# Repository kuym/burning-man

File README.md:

Burning Man 2015

aka Church of the Fifth Element
aka Home Sweet Dome
aka Burners on the Fence

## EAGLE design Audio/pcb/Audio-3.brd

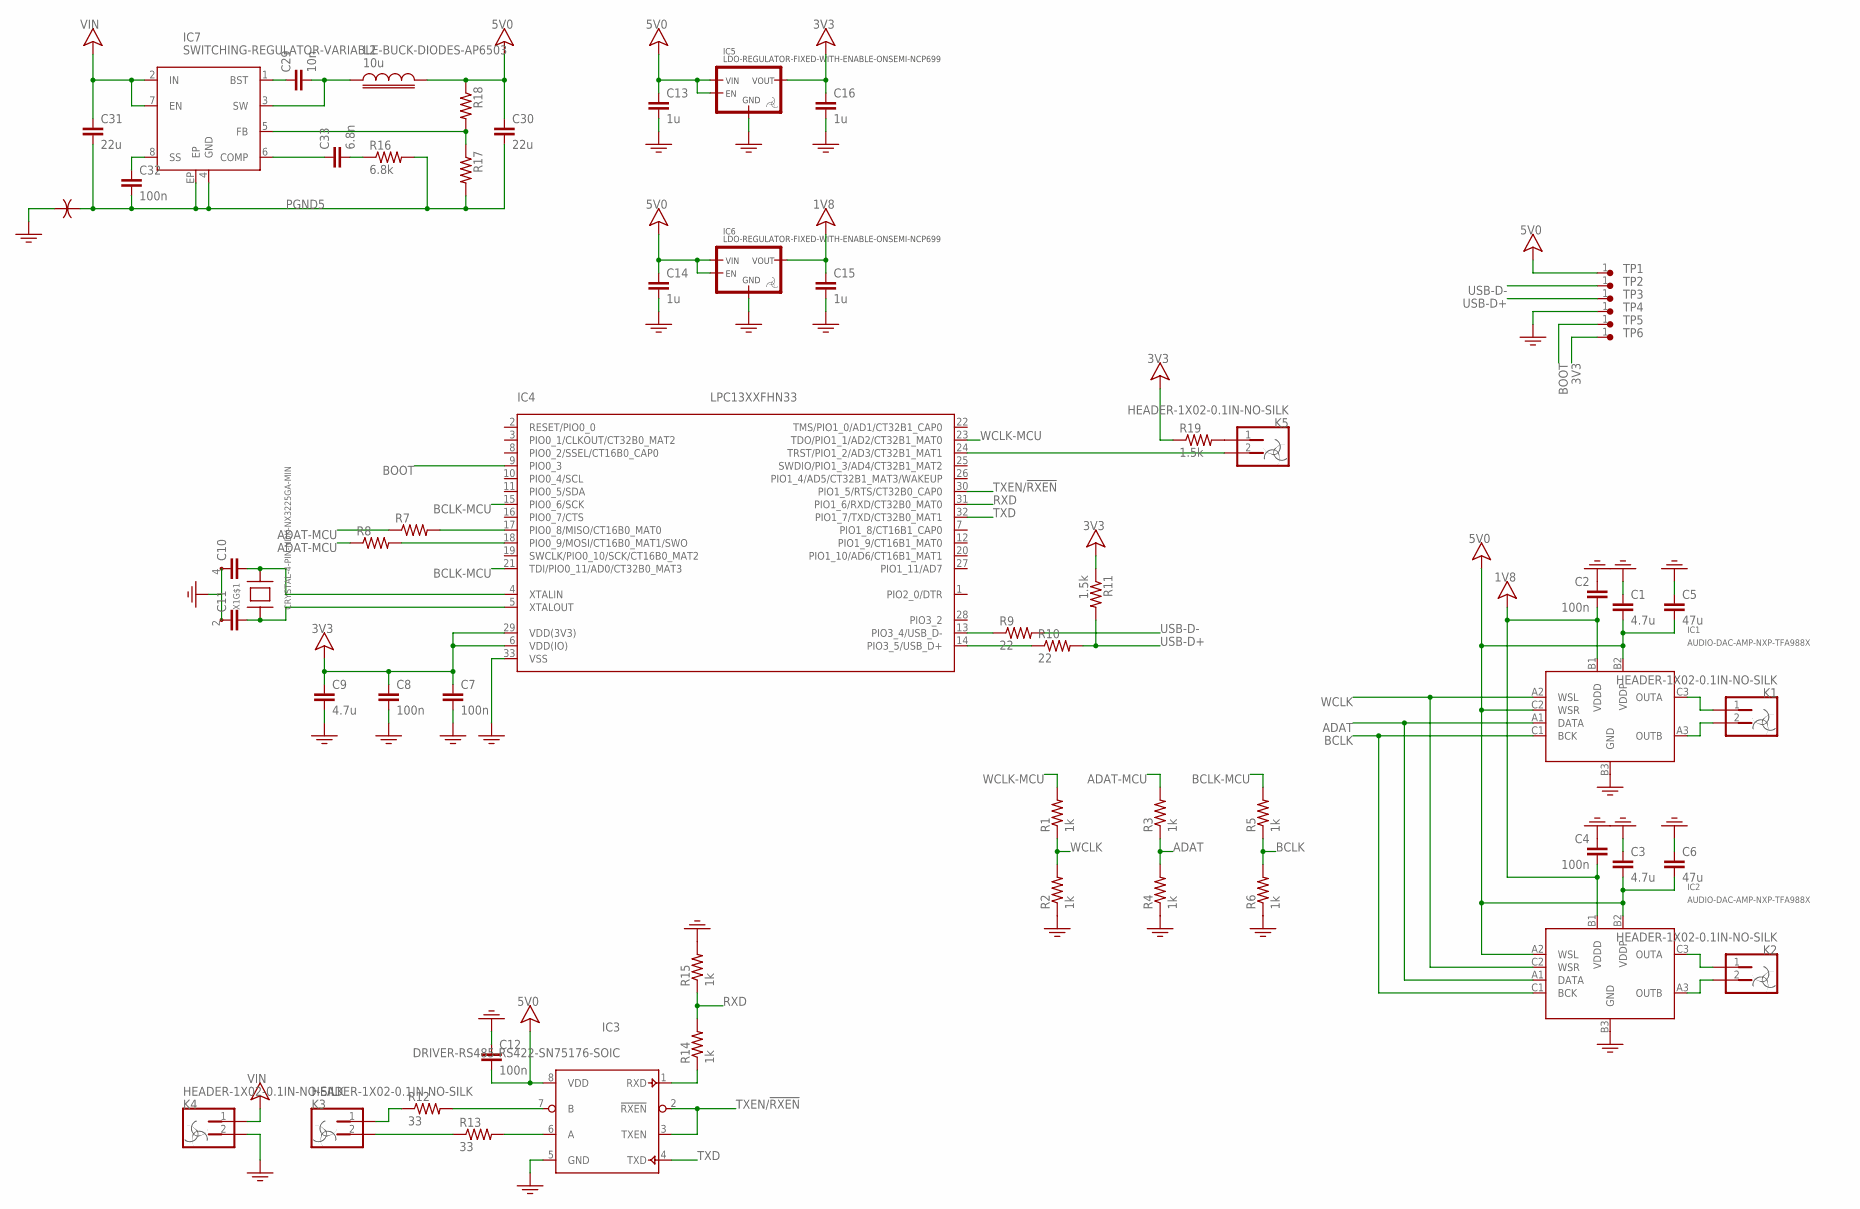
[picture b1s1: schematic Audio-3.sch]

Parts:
C1, C3, C9: 4.7u; 0603-MIN
C2, C4, C7, C8, C12, C32: 100n; 0603-MIN
C5, C6: 47u; 1206-MIN
C10, C11: CAP-0603-MIN; 0603-MIN
C13, C14, C15, C16: 1u; 0603-MIN
C29: 10n; 0603-MIN
C30, C31: 22u; 1206
C33: 6.8n; 0603-MIN
IC1, IC2: AUDIO-DAC-AMP-NXP-TFA988X; NXP-TFA988X-WLCSP9
IC3: DRIVER-RS485-RS422-SN75176-SOIC; EIAJ-SOIC8
IC4: LPC13XXFHN33; HVQFN33-7X7MM
IC5, IC6: LDO-REGULATOR-FIXED-WITH-ENABLE-ONSEMI-NCP699; SOT23-5
IC7: SWITCHING-REGULATOR-VARIABLE-BUCK-DIODES-AP6503; EIAJ-SOIC8-3.9MM-EXPOSED-PAD
K1, K2, K3, K4, K5: HEADER-1X02-0.1IN-NO-SILK; HEADER-1X02-NO-SILK
L2: 10u; 1210
R1, R2, R3, R4, R5, R6, R14, R15: 1k; 0603-MIN
R7, R8, R17, R18: RESISTOR-0603-MIN; 0603-MIN
R9, R10: 22; 0603-MIN
R11, R19: 1.5k; 0603-MIN
R12, R13: 33; 0805-MIN
R16: 6.8k; 0603-MIN
TP1, TP2, TP3, TP4, TP5, TP6: TEST-POINT-0.75MM
U4: GND-ISOLATOR-0.032"
X1: CRYSTAL-4-PIN-NDK-NX3225GA-MIN; CRYSTAL-NDK-NX3225GA-3X2.5MM-MIN

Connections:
1V8: C2.1, C4.1, C15.2, IC1.B1 (VDDD), IC2.B1 (VDDD), IC6.5 (VOUT)
3V3: C7.2, C8.2, C9.2, C16.2, IC4.6 (VDD(IO)), IC4.29 (VDD(3V3)), IC5.5 (VOUT), R11.1, R19.1, TP6.1
5V0: C1.1, C3.1, C5.1, C6.1, C12.1, C13.2, C14.2, C30.2, IC1.B2 (VDDP), IC1.C2 (WSR), IC2.A2 (WSL), IC2.B2 (VDDP), IC3.8 (VDD), IC5.1 (VIN), IC5.3 (EN), IC6.1 (VIN), IC6.3 (EN), L2.2, R18.1, TP1.1
5V0FB: IC7.5 (FB), R17.1, R18.2
ADAT: IC1.A1 (DATA), IC2.A1 (DATA), R3.1, R4.2
ADAT-MCU: R3.2, R7.1, R8.1
BCLK: IC1.C1 (BCK), IC2.C1 (BCK), R5.1, R6.2
BCLK-MCU: IC4.15 (PIO0_6/SCK), IC4.21 (TDI/PIO0_11/AD0/CT32B0_MAT3), R5.2
BOOT: IC4.9 (PIO0_3), TP5.1
GND: C1.2, C2.2, C3.2, C4.2, C5.2, C6.2, C7.1, C8.1, C9.1, C10.2, C11.2, C12.2, C13.1, C14.1, C15.1, C16.1, IC1.B3 (GND), IC2.B3 (GND), IC3.5 (GND), IC4.33 (VSS), IC5.2 (GND), IC6.2 (GND), K4.2, R2.1, R4.1, R6.1, R15.2, TP4.1, U4.B, X1.2 (1), X1.4 (1)
unnamed: IC4.17 (PIO0_8/MISO/CT16B0_MAT0), R7.2
unnamed: IC4.18 (PIO0_9/MOSI/CT16B0_MAT1/SWO), R8.2
unnamed: C10.1, IC4.4 (XTALIN), X1.3
unnamed: C11.1, IC4.5 (XTALOUT), X1.1
unnamed: IC4.13 (PIO3_4/USB_D-), R9.1
unnamed: IC4.14 (PIO3_5/USB_D+), R10.1
unnamed: IC3.7 (B), R12.2
unnamed: IC1.C3 (OUTA), K1.1
unnamed: IC1.A3 (OUTB), K1.2
unnamed: IC2.C3 (OUTA), K2.1
unnamed: IC2.A3 (OUTB), K2.2
unnamed: IC3.6 (A), R13.2
unnamed: C29.1, IC7.3 (SW), L2.1
unnamed: IC3.1 (RXD), R14.1
unnamed: C29.2, IC7.1 (BST)
unnamed: C33.2, IC7.6 (COMP)
unnamed: C33.1, R16.1
unnamed: K3.2, R13.1
unnamed: K3.1, R12.1
unnamed: C32.2, IC7.8 (SS)
unnamed: K5.1, R19.2
unnamed: IC4.24 (TRST/PIO1_2/AD3/CT32B1_MAT1), K5.2
PGND5: C30.1, C31.1, C32.1, IC7.4 (GND), IC7.EP, R16.2, R17.2, U4.A
RXD: IC4.31 (PIO1_6/RXD/CT32B0_MAT0), R14.2, R15.1
TXD: IC3.4 (TXD), IC4.32 (PIO1_7/TXD/CT32B0_MAT1)
TXEN/!RXEN: IC3.2 (!RXEN), IC3.3 (TXEN), IC4.30 (PIO1_5/RTS/CT32B0_CAP0)
USB-D+: R10.2, R11.2, TP3.1
USB-D-: R9.2, TP2.1
VIN: C31.2, IC7.2 (IN), IC7.7 (EN), K4.1
WCLK: IC1.A2 (WSL), IC2.C2 (WSR), R1.1, R2.2
WCLK-MCU: IC4.23 (TDO/PIO1_1/AD2/CT32B1_MAT0), R1.2

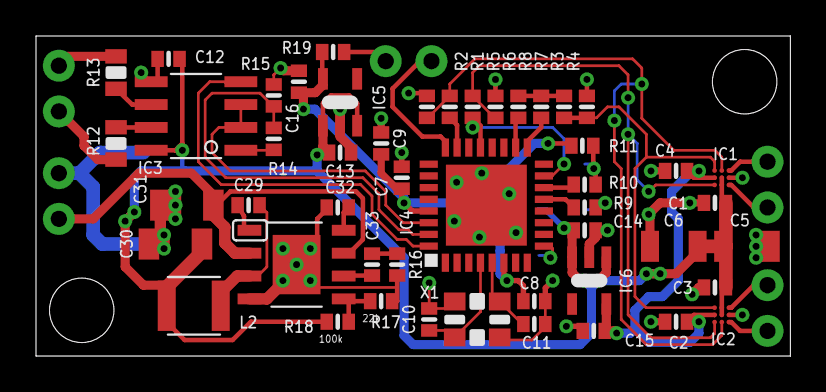
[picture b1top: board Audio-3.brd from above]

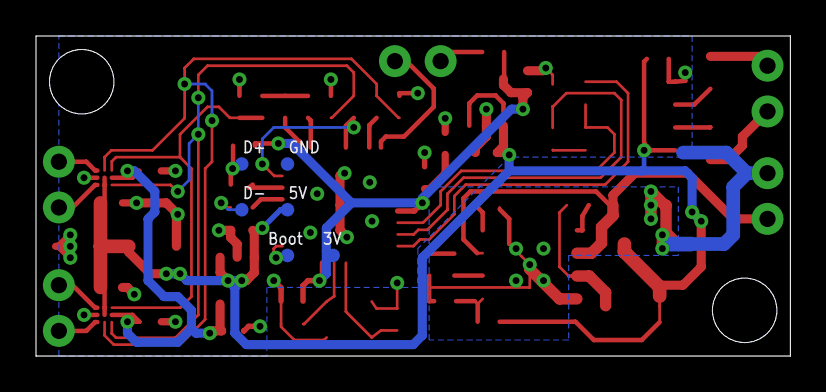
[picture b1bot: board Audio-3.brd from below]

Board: 2 copper layers, 41.9 x 17.8 mm, 61 parts (7 on the bottom side), 41 nets.

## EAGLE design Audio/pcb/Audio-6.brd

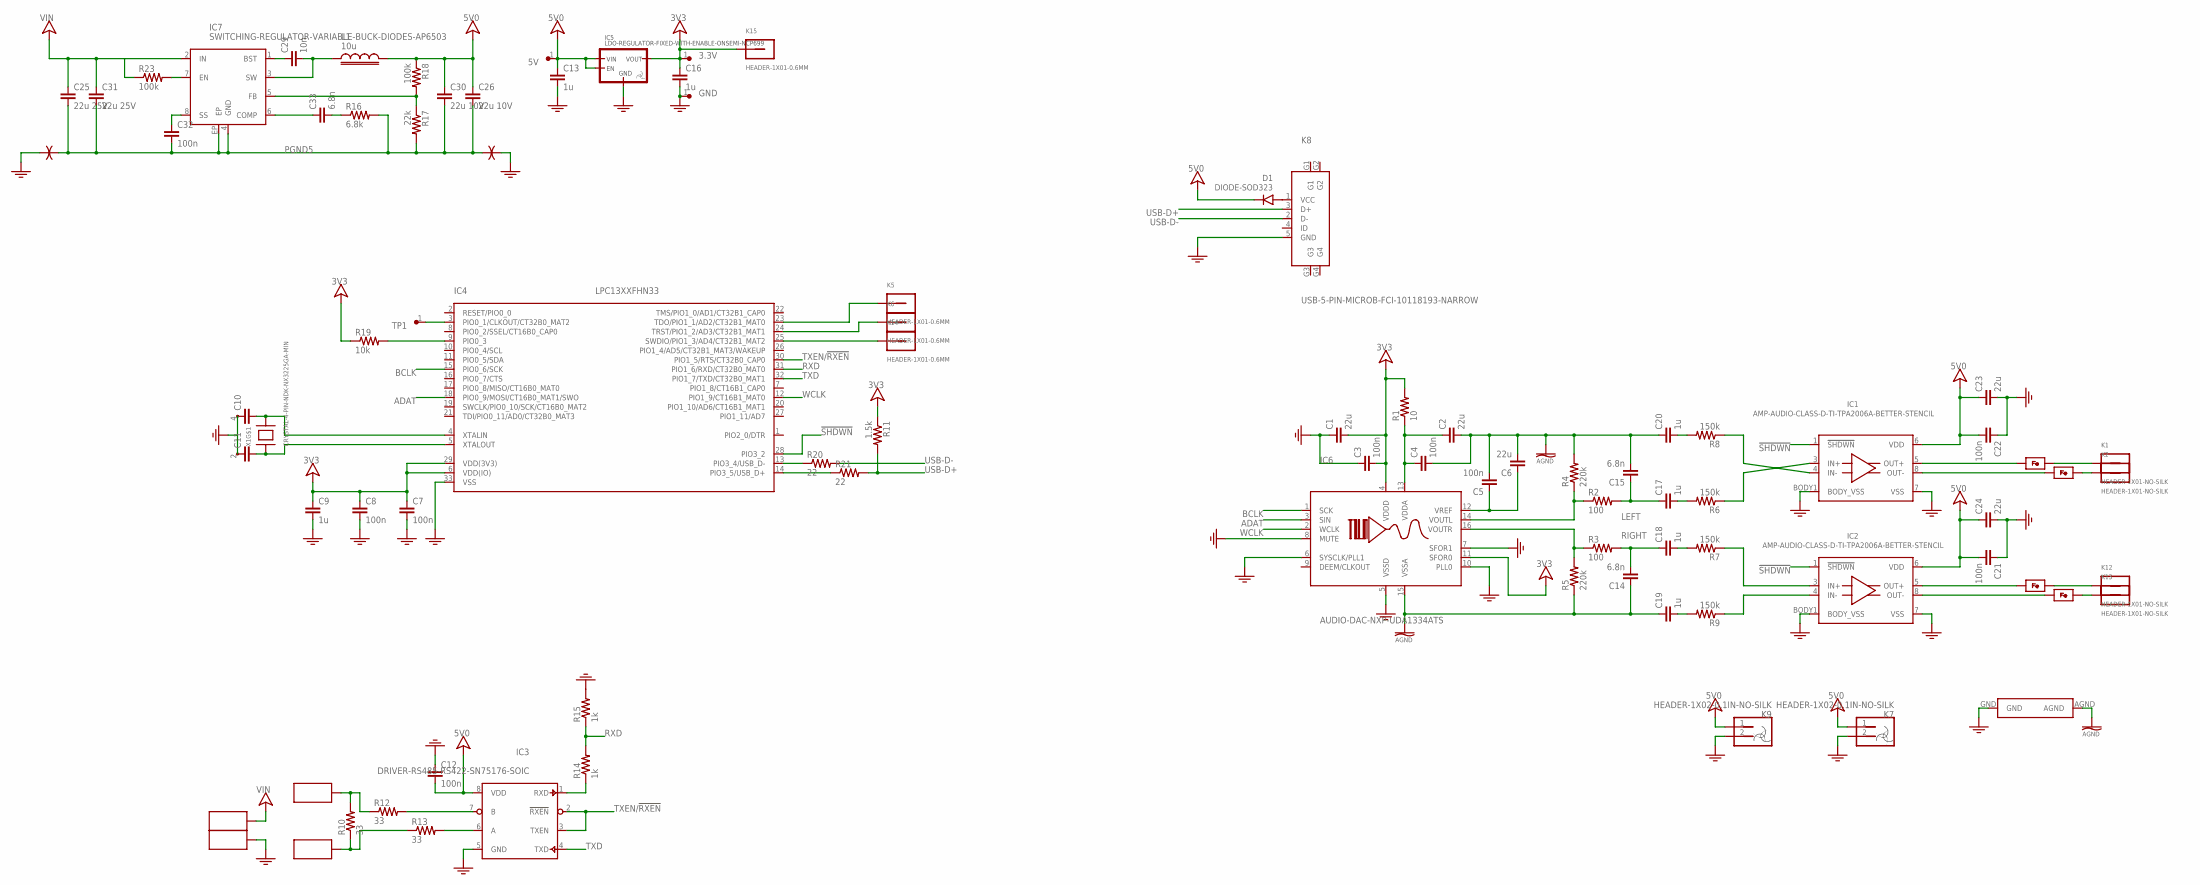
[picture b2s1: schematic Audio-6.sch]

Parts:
3.3V, 5V: TEST-POINT-0.75MM
C1, C2, C6, C23, C24: 22u; 1206-MIN
C3, C4, C5, C7, C8, C12, C21, C22, C32: 100n; 0603-MIN
C9, C13, C16, C17, C18, C19, C20: 1u; 0603-MIN
C10, C11: CAP-0603-MIN; 0603-MIN
C14, C15, C33: 6.8n; 0603-MIN
C25, C31: 22u 25V; 1206
C26, C30: 22u 10V; 1206
C29: 10n; 0603-MIN
D1: DIODE-SOD323; SOD323
FB1, FB2, FB3, FB4: FERRITE-BEAD-0603-MIN; 0603-MIN
GND: TEST-POINT-0.75MM
IC1, IC2: AMP-AUDIO-CLASS-D-TI-TPA2006A-BETTER-STENCIL; QFN8-3X3MM-TI-TPA200X-BETTER-STENCIL
IC3: DRIVER-RS485-RS422-SN75176-SOIC; EIAJ-SOIC8
IC4: LPC13XXFHN33; HVQFN33-7X7MM
IC5: LDO-REGULATOR-FIXED-WITH-ENABLE-ONSEMI-NCP699; SOT23-5
IC6: AUDIO-DAC-NXP-UDA1334ATS; TSSOP16
IC7: SWITCHING-REGULATOR-VARIABLE-BUCK-DIODES-AP6503; EIAJ-SOIC8-3.9MM-EXPOSED-PAD
K1, K2, K12, K13: HEADER-1X01-NO-SILK
K3, K4, K10, K11: SPEAKER-BLOCK
K5, K6, K14, K15: HEADER-1X01-0.6MM; HEADER-1X01-0.6MM-DIAM
K7, K9: HEADER-1X02-0.1IN-NO-SILK; HEADER-1X02-NO-SILK
K8: USB-5-PIN-MICROB-FCI-10118193-NARROW; USB-MICROB-FCI-10118193-NARROW
L1: 10u; INDUCTOR-SMD-6X6MM
R1: 10; 0603-MIN
R2, R3: 100; 0603-MIN
R4, R5: 220k; 0603-MIN
R6, R7, R8, R9: 150k; 0603-MIN
R10, R12, R13: 33; 0805-MIN
R11: 1.5k; 0603-MIN
R14, R15: 1k; 0603-MIN
R16: 6.8k; 0603-MIN
R17: 22k; 0603-MIN
R18, R23: 100k; 0603-MIN
R19: 10k; 0603-MIN
R20, R21: 22; 0603-MIN
TP1: TEST-POINT-0.75MM
U1, U4: GND-ISOLATOR-0.032"
U$4: GND-AGND-CONNECTION
X1: CRYSTAL-4-PIN-NDK-NX3225GA-MIN; CRYSTAL-NDK-NX3225GA-3X2.5MM-MIN

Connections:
3V3: 3.3V.1, C1.1, C3.1, C7.2, C8.2, C9.2, C16.2, IC4.6 (VDD(IO)), IC4.29 (VDD(3V3)), IC5.5 (VOUT), IC6.4 (VDDD), IC6.11 (SFOR0), K15.P$1, R1.2, R11.1, R19.1
5V0: 5V.1, C12.1, C13.2, C21.1, C22.1, C23.2, C24.2, C26.2, C30.2, D1.K, IC1.6 (VDD), IC2.6 (VDD), IC3.8 (VDD), IC5.1 (VIN), IC5.3 (EN), K7.1, K9.1, L1.2, R18.1
5V0FB: IC7.5 (FB), R17.1, R18.2
!SHDWN: IC1.1 (!SHDWN), IC2.1 (!SHDWN), IC4.28 (PIO3_2)
ADAT: IC4.18 (PIO0_9/MOSI/CT16B0_MAT1/SWO), IC6.3 (SIN)
AGND: C2.1, C4.1, C5.1, C6.1, C14.2, C15.1, C19.2, C20.2, IC6.15 (VSSA), R4.2, R5.1, U$4.AGND
BCLK: IC4.15 (PIO0_6/SCK), IC6.1 (SCK)
BOOT: IC4.3 (PIO0_1/CLKOUT/CT32B0_MAT2), TP1.1
D+: IC4.14 (PIO3_5/USB_D+), R21.1
D-: IC4.13 (PIO3_4/USB_D-), R20.1
GND: C1.2, C3.2, C7.1, C8.1, C9.1, C10.2, C11.2, C12.2, C13.1, C16.1, C21.2, C22.2, C23.1, C24.1, GND.1, IC1.7 (VSS), IC1.BODY1 (BODY_VSS), IC2.7 (VSS), IC2.BODY1 (BODY_VSS), IC3.5 (GND), IC4.33 (VSS), IC5.2 (GND), IC6.5 (VSSD), IC6.6 (SYSCLK/PLL1), IC6.7 (SFOR1), IC6.8 (MUTE), IC6.10 (PLL0), K4.P$1, K7.2, K8.5 (GND), K9.2, R15.2, U1.A, U4.B, U$4.GND, X1.2 (1), X1.4 (1)
IC1-: IC1.4 (IN-), R8.1
IC1OUT+: FB1.2, K1.1
IC1OUT-: FB2.2, K2.1
IC1SE: IC6.14 (VOUTL), R2.1, R4.1
IC2+: IC2.3 (IN+), R7.1
IC2-: IC2.4 (IN-), R9.1
IC2OUT+: FB3.2, K12.1
IC2OUT-: FB4.2, K13.1
IC2SE: IC6.16 (VOUTR), R3.1, R5.2
IO1: IC4.23 (TDO/PIO1_1/AD2/CT32B1_MAT0), K5.P$1
IO2: IC4.24 (TRST/PIO1_2/AD3/CT32B1_MAT1), K6.P$1
IO3: IC4.25 (SWDIO/PIO1_3/AD4/CT32B1_MAT2), K14.P$1
LEFT: C15.2, C17.2, R2.2
unnamed: IC1.3 (IN+), R6.1
unnamed: IC4.9 (PIO0_3), R19.2
unnamed: C10.1, IC4.4 (XTALIN), X1.3
unnamed: C11.1, IC4.5 (XTALOUT), X1.1
unnamed: IC3.7 (B), R12.2
unnamed: C17.1, R6.2
unnamed: C18.1, R7.2
unnamed: IC3.6 (A), R13.2
unnamed: C29.1, IC7.3 (SW), L1.1
unnamed: IC3.1 (RXD), R14.1
unnamed: C29.2, IC7.1 (BST)
unnamed: C33.2, IC7.6 (COMP)
unnamed: C33.1, R16.1
unnamed: C32.2, IC7.8 (SS)
unnamed: D1.A, K8.1 (VCC)
unnamed: C2.2, C4.2, IC6.13 (VDDA), R1.1
unnamed: IC7.7 (EN), R23.2
unnamed: C19.1, R9.2
unnamed: C20.1, R8.2
unnamed: FB1.1, IC1.5 (OUT+)
unnamed: FB2.1, IC1.8 (OUT-)
unnamed: FB3.1, IC2.5 (OUT+)
unnamed: FB4.1, IC2.8 (OUT-)
PGND5: C25.1, C26.1, C30.1, C31.1, C32.1, IC7.4 (GND), IC7.EP, R16.2, R17.2, U1.B, U4.A
RIGHT: C14.1, C18.2, R3.2
RS485D+: K11.P$1, R10.1, R13.1
RS485D-: K10.P$1, R10.2, R12.1
RXD: IC4.31 (PIO1_6/RXD/CT32B0_MAT0), R14.2, R15.1
TXD: IC3.4 (TXD), IC4.32 (PIO1_7/TXD/CT32B0_MAT1)
TXEN/!RXEN: IC3.2 (!RXEN), IC3.3 (TXEN), IC4.30 (PIO1_5/RTS/CT32B0_CAP0)
USB-D+: K8.3 (D+), R11.2, R21.2
USB-D-: K8.2 (D-), R20.2
VIN: C25.2, C31.2, IC7.2 (IN), K3.P$1, R23.1
VREF: C5.2, C6.2, IC6.12 (VREF)
WCLK: IC4.12 (PIO1_9/CT16B1_MAT0), IC6.2 (WCLK)

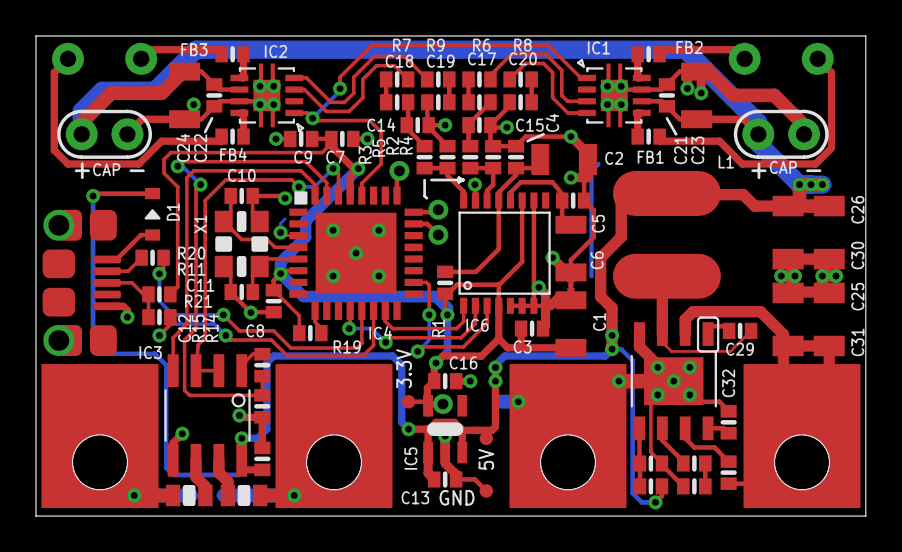
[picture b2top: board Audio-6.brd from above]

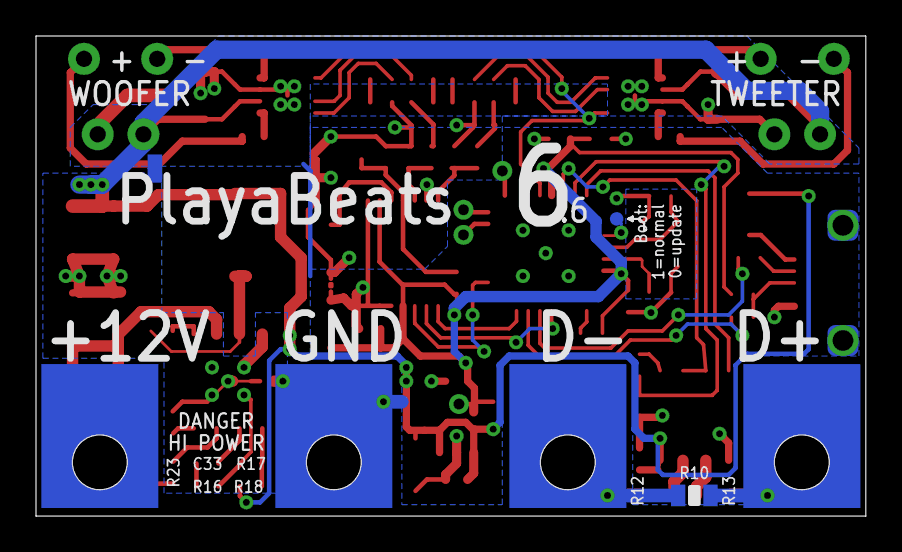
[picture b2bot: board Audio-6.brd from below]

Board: 2 copper layers, 46.1 x 26.7 mm, 89 parts (7 on the bottom side), 59 nets.

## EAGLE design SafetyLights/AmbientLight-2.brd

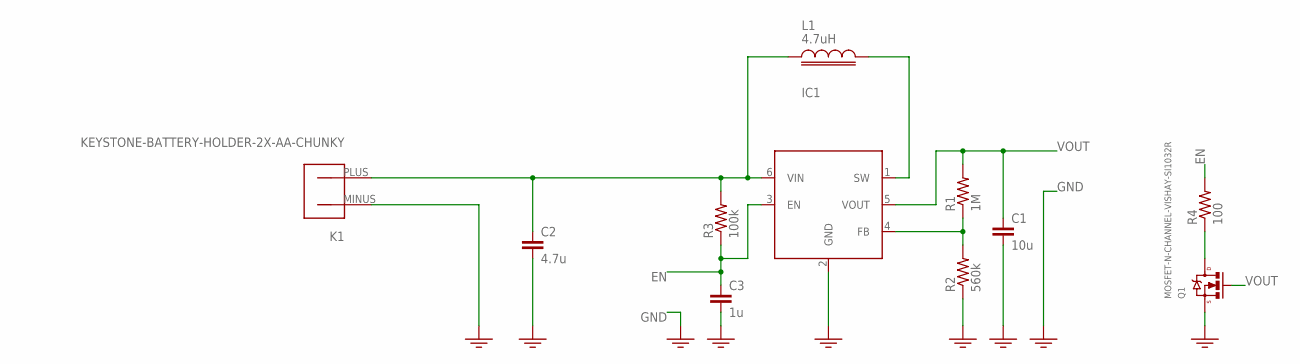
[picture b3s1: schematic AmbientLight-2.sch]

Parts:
C1: 10u; 0805-WIDE
C2: 4.7u; 0603-MIN
C3: 1u; 0603-MIN
IC1: SWITCHING-REGULATOR-VARIABLE-BOOST-MCP1640; SOT23-6
K1: KEYSTONE-BATTERY-HOLDER-2X-AA-CHUNKY
L1: 4.7uH; 1210-INDUCTOR-MIN
Q1: MOSFET-N-CHANNEL-VISHAY-SI1032R; SC-75A
R1: 1M; 0603-MIN
R2: 560k; 0603-MIN
R3: 100k; 0603-MIN
R4: 100; 0603-MIN

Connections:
EN: C3.2, IC1.3 (EN), R3.1, R4.2
GND: C1.1, C2.1, C3.1, IC1.2 (GND), K1.MINUS (PLUS), Q1.2 (SOURCE), R2.1
unnamed: Q1.3 (DRAIN), R4.1
VBAT: C2.2, IC1.6 (VIN), K1.PLUS (MINUS), L1.1, R3.2
VFB: IC1.4 (FB), R1.1, R2.2
VOUT: C1.2, IC1.5 (VOUT), Q1.1 (GATE), R1.2
VSW: IC1.1 (SW), L1.2

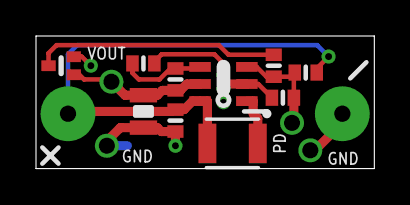
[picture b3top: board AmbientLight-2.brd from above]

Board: 2 copper layers, 18.8 x 7.4 mm, 11 parts (0 on the bottom side), 7 nets.

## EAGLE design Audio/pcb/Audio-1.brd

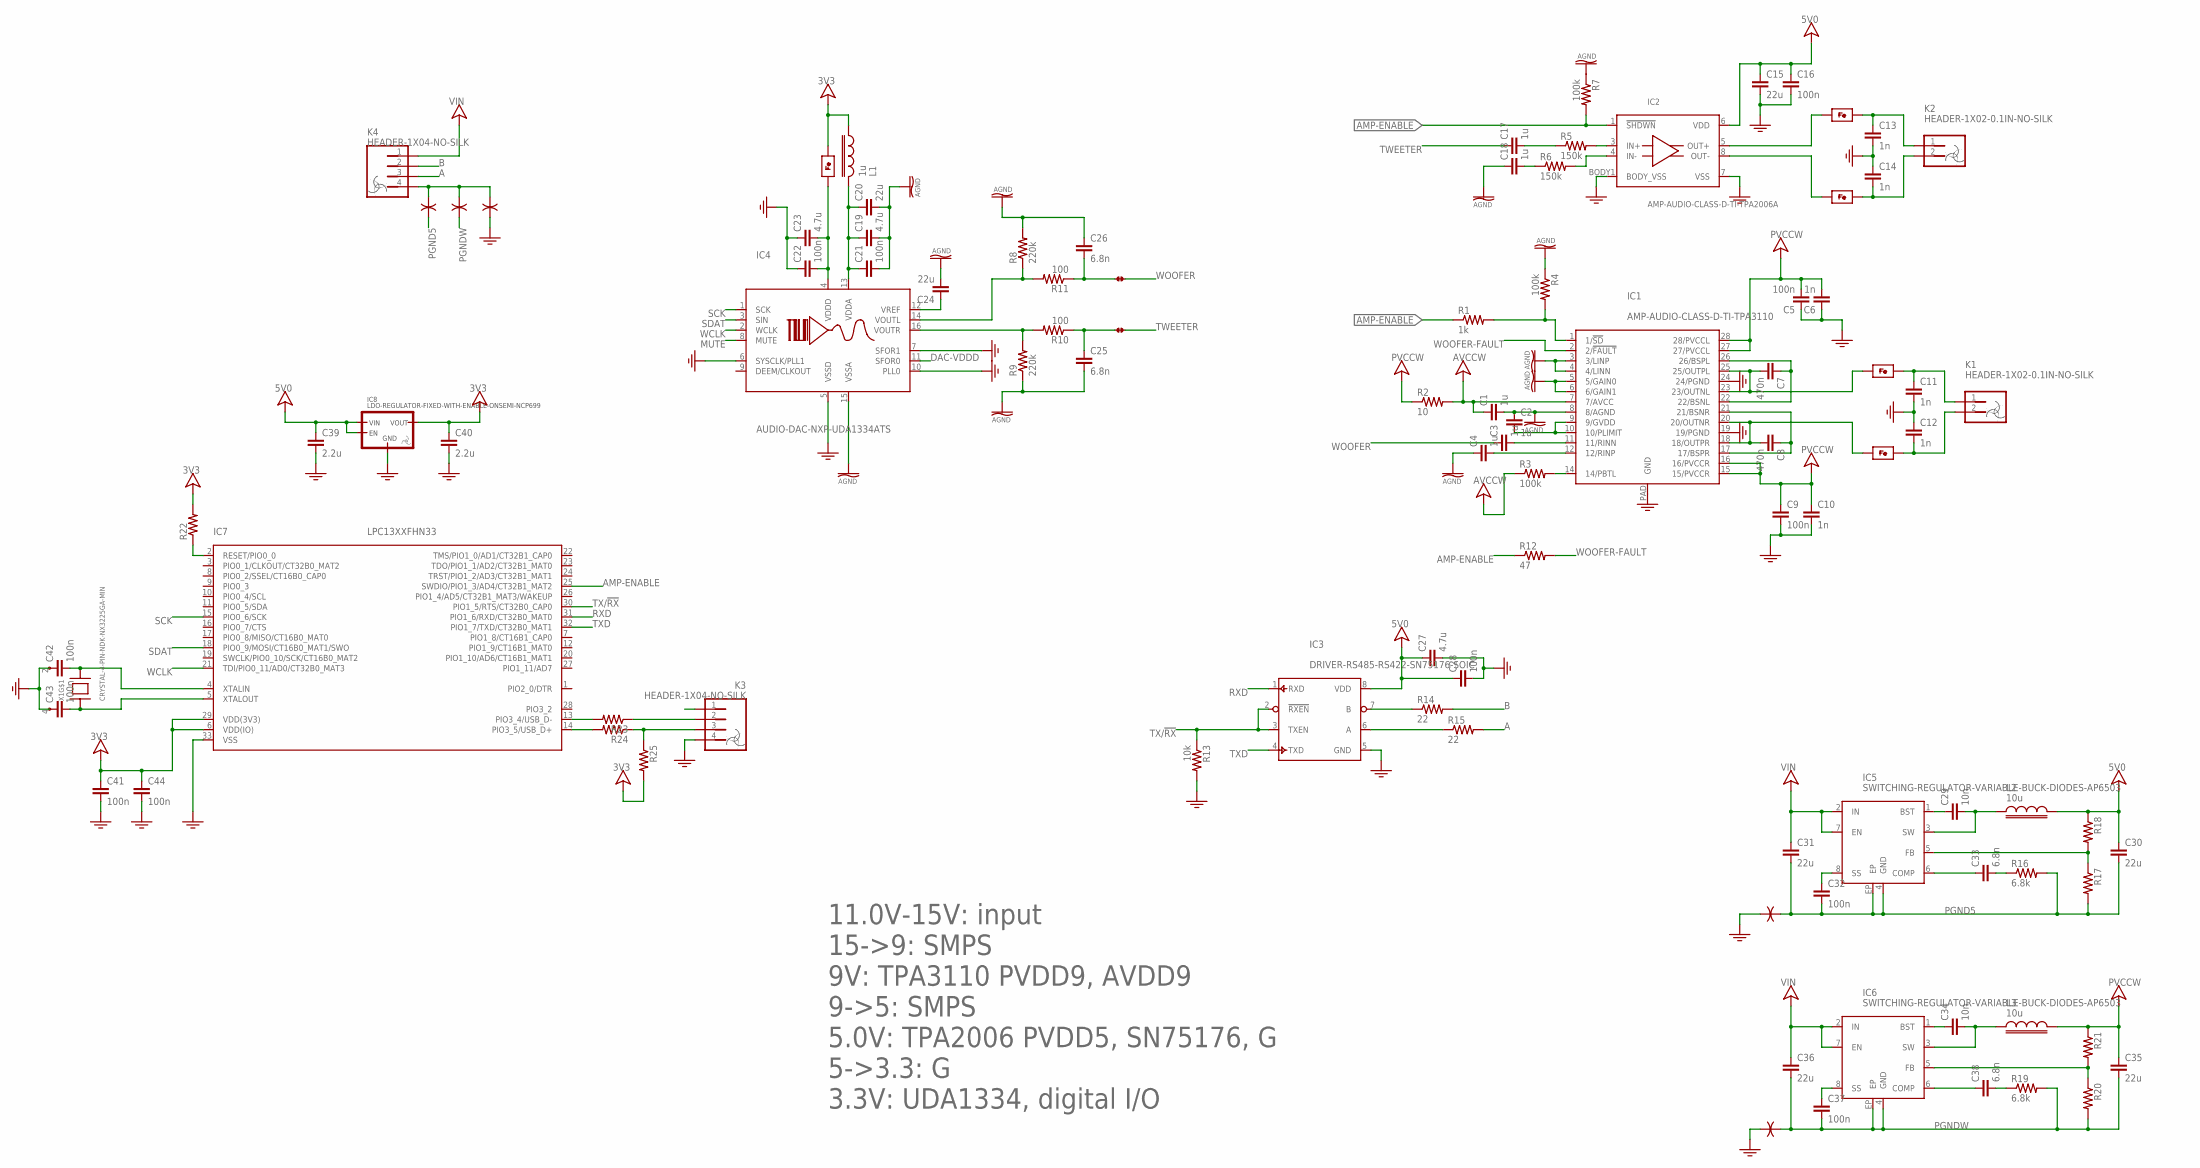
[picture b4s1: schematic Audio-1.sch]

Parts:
C1, C2, C3, C4, C17, C18: 1u; 0603-MIN
C5, C9, C16, C21, C22, C28, C32, C37, C41, C42, C43, C44: 100n; 0603-MIN
C6, C10, C11, C12, C13, C14: 1n; 0603-MIN
C7, C8: 470n; 0603-MIN
C15, C20, C24: 22u; 1206-MIN
C19, C23: 4.7u; 0805-WIDE
C25, C26: 6.8n; 0603
C27: 4.7u; 0805
C29, C34: 10n; 0603-MIN
C30, C31, C35, C36: 22u; 1206
C33, C38: 6.8n; 0603-MIN
C39, C40: 2.2u; 0603-MIN
FB1, FB2, FB3, FB4, FB5: FERRITE-BEAD-0603-MIN; 0603-MIN
IC1: AMP-AUDIO-CLASS-D-TI-TPA3110; SSOP28-5.3MM-POWERPAD
IC2: AMP-AUDIO-CLASS-D-TI-TPA2006A; QFN8-3X3MM-TI-TPA200X
IC3: DRIVER-RS485-RS422-SN75176-SOIC; EIAJ-SOIC8
IC4: AUDIO-DAC-NXP-UDA1334ATS; TSSOP16
IC5, IC6: SWITCHING-REGULATOR-VARIABLE-BUCK-DIODES-AP6503; EIAJ-SOIC8-3.9MM-EXPOSED-PAD
IC7: LPC13XXFHN33; HVQFN33-7X7MM
IC8: LDO-REGULATOR-FIXED-WITH-ENABLE-ONSEMI-NCP699; SOT23-5
J1, J2: JUMPER-0805; 0805-JUMPER
K1, K2: HEADER-1X02-0.1IN-NO-SILK; HEADER-1X02-NO-SILK
K3, K4: HEADER-1X04-NO-SILK
L1: 1u; 0805-MIN
L2, L3: 10u; 1210
R1: 1k; 0603-MIN
R2: 10; 0603-MIN
R3, R4, R7: 100k; 0603-MIN
R5, R6: 150k; 0603-MIN
R8, R9: 220k; 0603
R10, R11: 100; 0603
R12: 47; 0603-MIN
R13: 10k; 0603-MIN
R14, R15: 22; 0805-MIN
R16, R19: 6.8k; 0603-MIN
R17, R18, R20, R21, R22, R23, R24, R25: RESISTOR-0603-MIN; 0603-MIN
U1, U2, U3, U4, U5: GND-ISOLATOR-0.032"
X1: CRYSTAL-4-PIN-NDK-NX3225GA-MIN; CRYSTAL-NDK-NX3225GA-3X2.5MM-MIN

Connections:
3V3: C40.2, C41.2, C44.2, FB5.2, IC7.6 (VDD(IO)), IC7.29 (VDD(3V3)), IC8.5 (VOUT), L1.2, R22.2, R25.2
5V0: C15.2, C16.2, C27.2, C28.2, C30.2, C39.2, IC2.6 (VDD), IC3.8 (VDD), IC8.1 (VIN), IC8.3 (EN), L2.2, R18.1
5V0FB: IC5.5 (FB), R17.1, R18.2
!WOOFER-SD: IC1.1 (1/!SD), R1.2, R4.2
A: K4.3, R15.2
AGND: C1.1, C2.2, C4.2, C18.2, C19.1, C20.1, C21.1, C24.1, C25.1, C26.2, IC1.3 (3/LINP), IC1.4 (4/LINN), IC1.5 (5/GAIN0), IC1.6 (6/GAIN1), IC1.8 (8/AGND), IC4.15 (VSSA), R4.1, R7.1, R8.2, R9.1
AMP-ENABLE: IC2.1 (!SHDWN), IC7.25 (SWDIO/PIO1_3/AD4/CT32B1_MAT2), R1.1, R7.2, R12.1
AVCCW: C1.2, IC1.7 (7/AVCC), R2.2, R3.1
B: K4.2, R14.2
BSL: C7.2, IC1.22 (22/BSNL), IC1.26 (26/BSPL)
BSR: C8.2, IC1.17 (17/BSPR), IC1.21 (21/BSNR)
D+: K3.3, R24.1, R25.1
D-: K3.2, R23.1
DAC-TO: C25.2, J2.1, R10.1
DAC-VDDA: C19.2, C20.2, C21.2, IC4.13 (VDDA), L1.1
DAC-VDDD: C22.1, C23.1, FB5.1, IC4.4 (VDDD), IC4.11 (SFOR0)
DAC-VOUT-TO: IC4.16 (VOUTR), R9.2, R10.2
DAC-VOUT-WO: IC4.14 (VOUTL), R8.1, R11.2
DAC-WO: C26.1, J1.1, R11.1
GND: C5.2, C6.2, C9.1, C10.1, C11.1, C12.2, C13.1, C14.2, C15.1, C16.1, C22.2, C23.2, C27.1, C28.1, C39.1, C40.1, C41.1, C42.2, C43.2, C44.1, IC1.19 (19/PGND), IC1.24 (24/PGND), IC1.PAD (GND), IC2.7 (VSS), IC2.BODY1 (BODY_VSS), IC3.5 (GND), IC4.5 (VSSD), IC4.6 (SYSCLK/PLL1), IC4.7 (SFOR1), IC4.10 (PLL0), IC7.33 (VSS), IC8.2 (GND), K3.4, R13.2, U3.A, U4.B, U5.B, X1.2 (1), X1.4 (1)
GVDD: C2.1, IC1.9 (9/GVDD), IC1.10 (10/PLIMIT)
MUTE: IC4.8 (MUTE)
unnamed: IC3.7 (B), R14.1
unnamed: C24.2, IC4.12 (VREF)
unnamed: IC3.6 (A), R15.1
unnamed: C29.1, IC5.3 (SW), L2.1
unnamed: C29.2, IC5.1 (BST)
unnamed: C34.1, IC6.3 (SW), L3.1
unnamed: C34.2, IC6.1 (BST)
unnamed: FB3.1, IC2.5 (OUT+)
unnamed: IC1.14 (14/PBTL), R3.2
unnamed: C38.2, IC6.6 (COMP)
unnamed: C33.2, IC5.6 (COMP)
unnamed: FB4.1, IC2.8 (OUT-)
unnamed: C14.1, FB4.2, K2.2
unnamed: C13.2, FB3.2, K2.1
unnamed: C33.1, R16.1
unnamed: C38.1, R19.1
unnamed: C32.2, IC5.8 (SS)
unnamed: C37.2, IC6.8 (SS)
unnamed: IC7.2 (RESET/PIO0_0), R22.1
unnamed: IC2.3 (IN+), R5.2
unnamed: IC2.4 (IN-), R6.2
unnamed: C18.1, R6.1
unnamed: C17.1, R5.1
unnamed: IC7.13 (PIO3_4/USB_D-), R23.2
unnamed: IC7.14 (PIO3_5/USB_D+), R24.2
unnamed: C43.1, IC7.5 (XTALOUT), X1.1
unnamed: C42.1, IC7.4 (XTALIN), X1.3
unnamed: K4.4, U1.B, U2.B, U3.B
OUTL: C7.1, FB1.1, IC1.23 (23/OUTNL), IC1.25 (25/OUTPL)
OUTR: C8.1, FB2.1, IC1.18 (18/OUTPR), IC1.20 (20/OUTNR)
PGND5: C30.1, C31.1, C32.1, IC5.4 (GND), IC5.EP, R16.2, R17.2, U1.A, U4.A
PGNDW: C35.1, C36.1, C37.1, IC6.4 (GND), IC6.EP, R19.2, R20.2, U2.A, U5.A
PVCCW: C5.1, C6.1, C9.2, C10.2, C35.2, IC1.15 (15/PVCCR), IC1.16 (16/PVCCR), IC1.27 (27/PVCCL), IC1.28 (28/PVCCL), L3.2, R2.1, R21.1
RINN: C3.1, IC1.11 (11/RINN)
RINP: C4.1, IC1.12 (12/RINP)
RXD: IC3.1 (RXD), IC7.31 (PIO1_6/RXD/CT32B0_MAT0)
SCK: IC4.1 (SCK), IC7.15 (PIO0_6/SCK)
SDAT: IC4.3 (SIN), IC7.18 (PIO0_9/MOSI/CT16B0_MAT1/SWO)
TWEETER: C17.2, J2.2
TX/!RX: IC3.2 (!RXEN), IC3.3 (TXEN), IC7.30 (PIO1_5/RTS/CT32B0_CAP0), R13.1
TXD: IC3.4 (TXD), IC7.32 (PIO1_7/TXD/CT32B0_MAT1)
VIN: C31.2, C36.2, IC5.2 (IN), IC5.7 (EN), IC6.2 (IN), IC6.7 (EN), K4.1
WCLK: IC4.2 (WCLK), IC7.21 (TDI/PIO0_11/AD0/CT32B0_MAT3)
WFB: IC6.5 (FB), R20.1, R21.2
WOOFER: C3.2, J1.2
WOOFER-FAULT: IC1.2 (2/!FAULT), R12.2
WOOFERL: C11.2, FB1.2, K1.1
WOOFERR: C12.1, FB2.2, K1.2

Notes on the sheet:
11.0V-15V: input 15->9: SMPS 9V: TPA3110 PVDD9, AVDD9 9->5: SMPS 5.0V: TPA2006 PVDD5, SN75176, G 5->3.3: G 3.3V: UDA1334, digital I/O

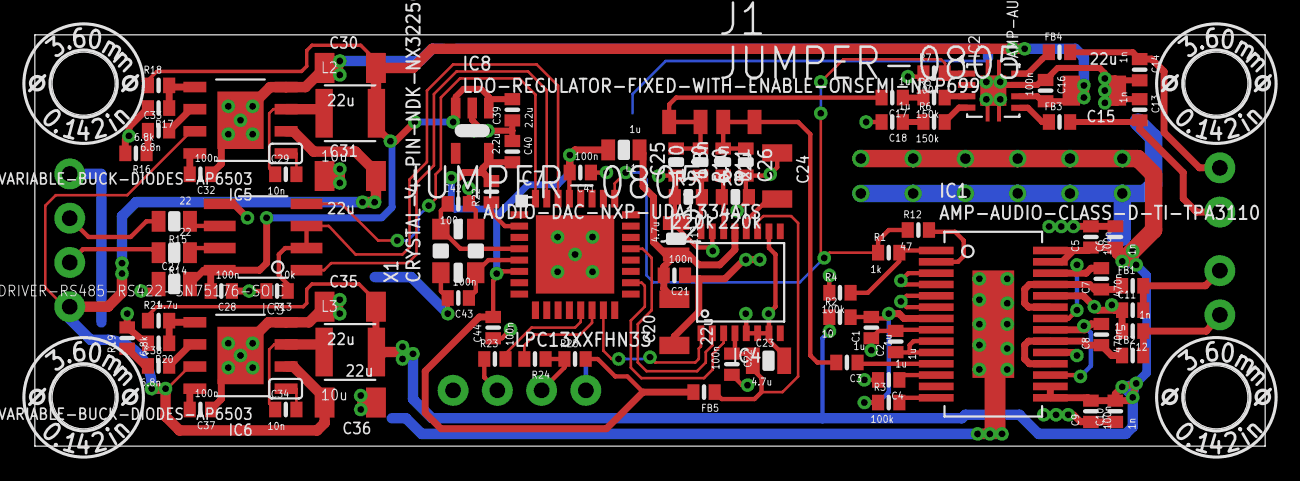
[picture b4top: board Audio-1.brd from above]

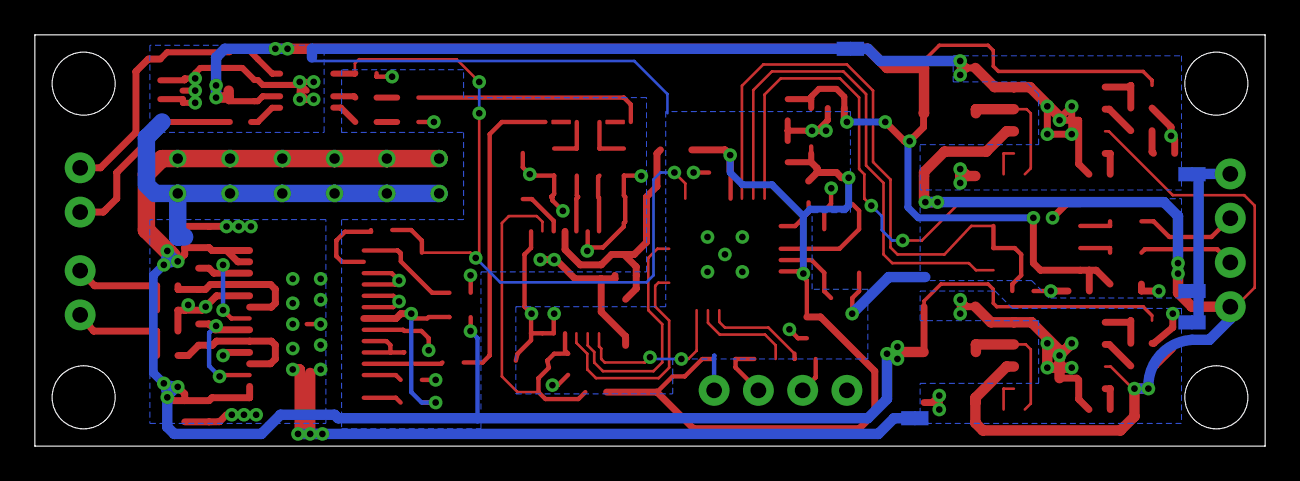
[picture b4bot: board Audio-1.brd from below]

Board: 2 copper layers, 70.6 x 23.6 mm, 101 parts (5 on the bottom side), 69 nets.

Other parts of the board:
U$1, U$9, U$10, U$16: MOUNTING-HOLE-3.6MM-LABELLED-DIAM

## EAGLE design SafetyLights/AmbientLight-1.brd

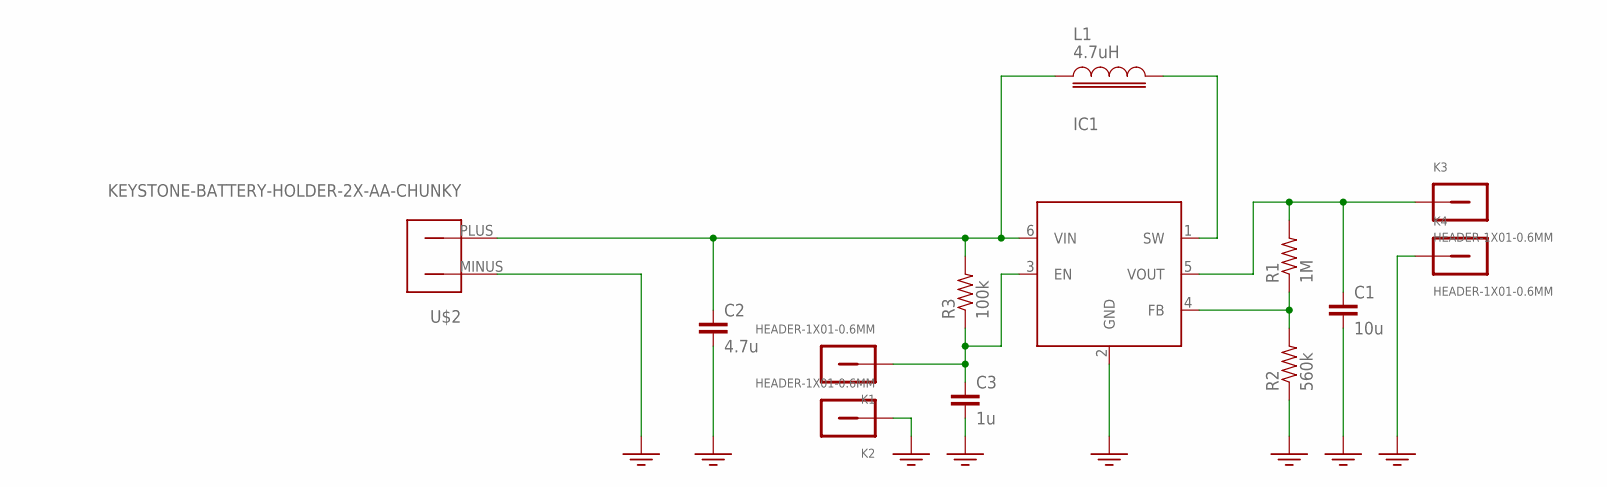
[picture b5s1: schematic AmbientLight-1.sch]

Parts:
C1: 10u; 0805-WIDE
C2: 4.7u; 0603-MIN
C3: 1u; 0603-MIN
IC1: SWITCHING-REGULATOR-VARIABLE-BOOST-MCP1640; SOT23-6
K1, K2, K3, K4: HEADER-1X01-0.6MM; HEADER-1X01-0.6MM-DIAM
L1: 4.7uH; 1210-INDUCTOR-MIN
R1: 1M; 0603-MIN
R2: 560k; 0603-MIN
R3: 100k; 0603-MIN
U$2: KEYSTONE-BATTERY-HOLDER-2X-AA-CHUNKY

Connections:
EN: C3.2, IC1.3 (EN), K1.P$1, R3.1
GND: C1.1, C2.1, C3.1, IC1.2 (GND), K2.P$1, K4.P$1, R2.1, U$2.MINUS (PLUS)
VBAT: C2.2, IC1.6 (VIN), L1.1, R3.2, U$2.PLUS (MINUS)
VFB: IC1.4 (FB), R1.1, R2.2
VOUT: C1.2, IC1.5 (VOUT), K3.P$1, R1.2
VSW: IC1.1 (SW), L1.2

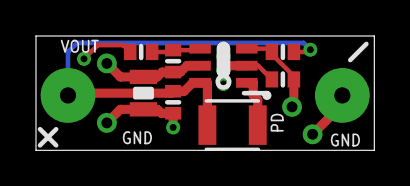
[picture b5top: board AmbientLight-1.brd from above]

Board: 2 copper layers, 18.8 x 6.3 mm, 13 parts (0 on the bottom side), 6 nets.

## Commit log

2015-08-18 Fridge design updated for new materials and dimensions, AmbientLight-2 and Audio-6 updated for manufacturability
2015-08-18 Added solar charge control box photo
2015-08-18 Fixing file permissions
2015-10-09 Updates to ambient audio etc.
2015-10-09 Added presentation from Hackaday Hardware Developer's Didactic Galactic #08
2015-10-09 Added pdf of HDDG #08 presentation

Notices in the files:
SafetyLights/AmbientLight-2.brd:
(C) 2015 Kuy Mainwaring
